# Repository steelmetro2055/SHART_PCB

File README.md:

Printed Circuit Board for AeroBing Designed in KiCAD EDA

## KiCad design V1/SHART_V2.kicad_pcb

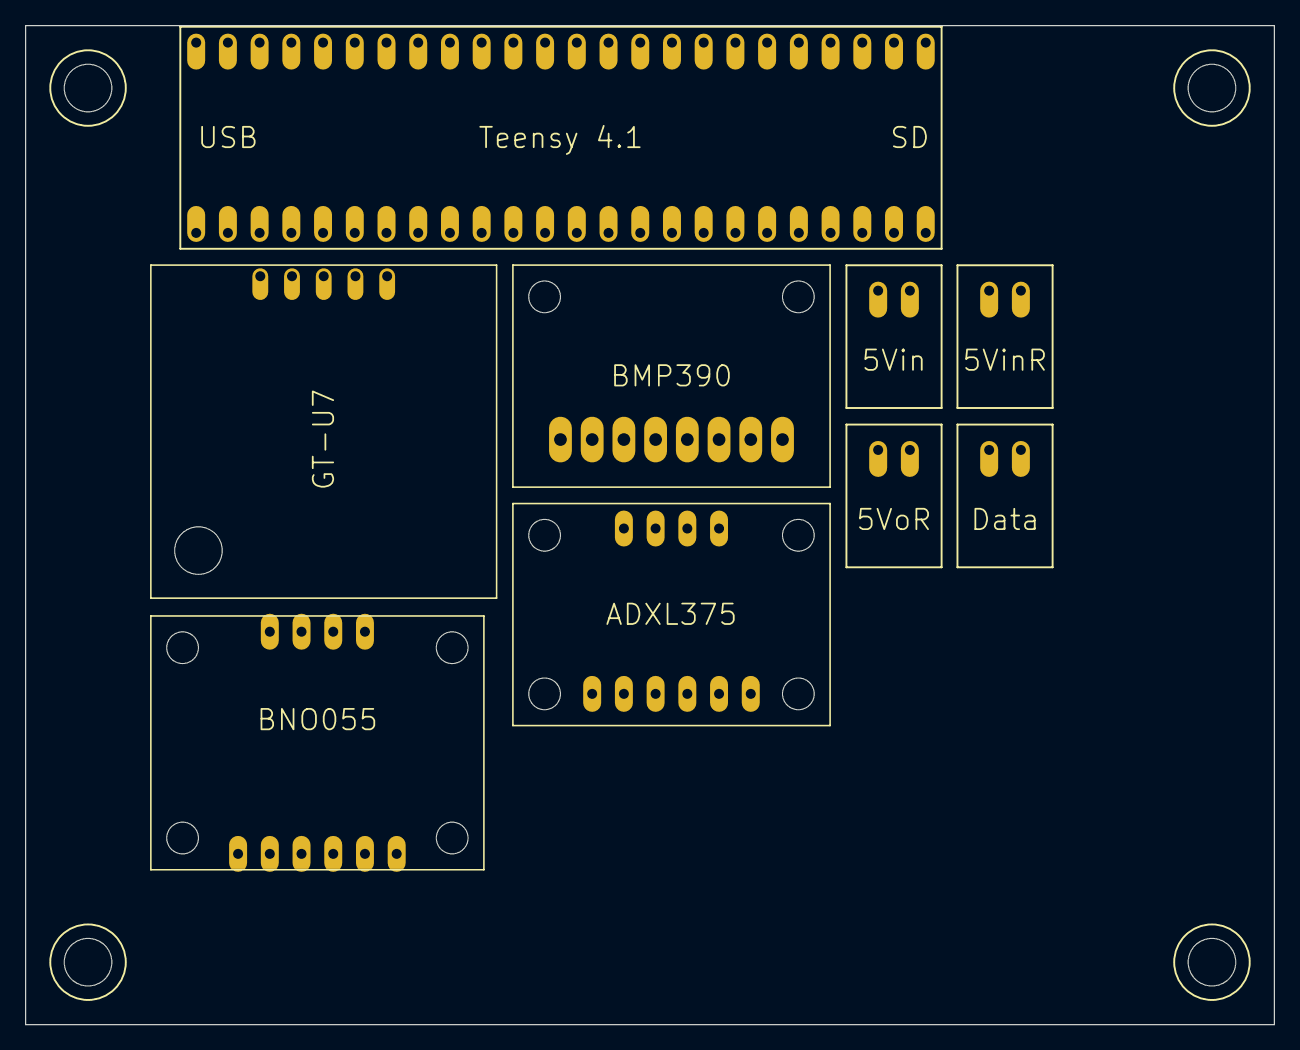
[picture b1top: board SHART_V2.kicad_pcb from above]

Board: 2 copper layers, 100.0 x 80.0 mm, 11 parts (0 on the bottom side), 14 nets, no tracks yet.

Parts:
@HOLE1, @HOLE1#2, @HOLE1#3, @HOLE1#4: (no value)
U$1: CUSTOM_TEENSY4.1
U$2: BMP390
U$3: BNO055
U$4: CUSTOM_POWER_INPUT
U$5: CUSTOM_RADIO_INTERFACE
U$6: GT-U7
U$7: ADXL375

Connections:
unnamed: U$1.5VA (5V), U$3.VIN, U$4.RFD_5V, U$6.VCC
unnamed: U$1.0, U$2.CS
unnamed: U$1.3VA, U$7.VIN
unnamed: U$1.3VB, U$2.VIN
unnamed: U$1.7, U$6.TX
unnamed: U$1.8, U$6.RX
unnamed: U$1.11, U$2.SDA, U$7.SDIO
unnamed: U$1.13, U$2.SCL, U$7.SCL
unnamed: U$1.16, U$3.SCL
unnamed: U$1.17, U$3.SDA
unnamed: U$1.37, U$7.CS
unnamed: U$1.12, U$2.SDC (SDO), U$7.SDO
unnamed: U$1.29, U$5.RX (RFD)
unnamed: U$1.28, U$5.TX (RFD)

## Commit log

2024-04-04 README.md
2024-04-04 Create Version One Details
2024-04-06 Create g
2024-06-17 Create Mand
